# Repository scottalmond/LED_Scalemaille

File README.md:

# LED_Scalemaille
Neopixel Scalemaille

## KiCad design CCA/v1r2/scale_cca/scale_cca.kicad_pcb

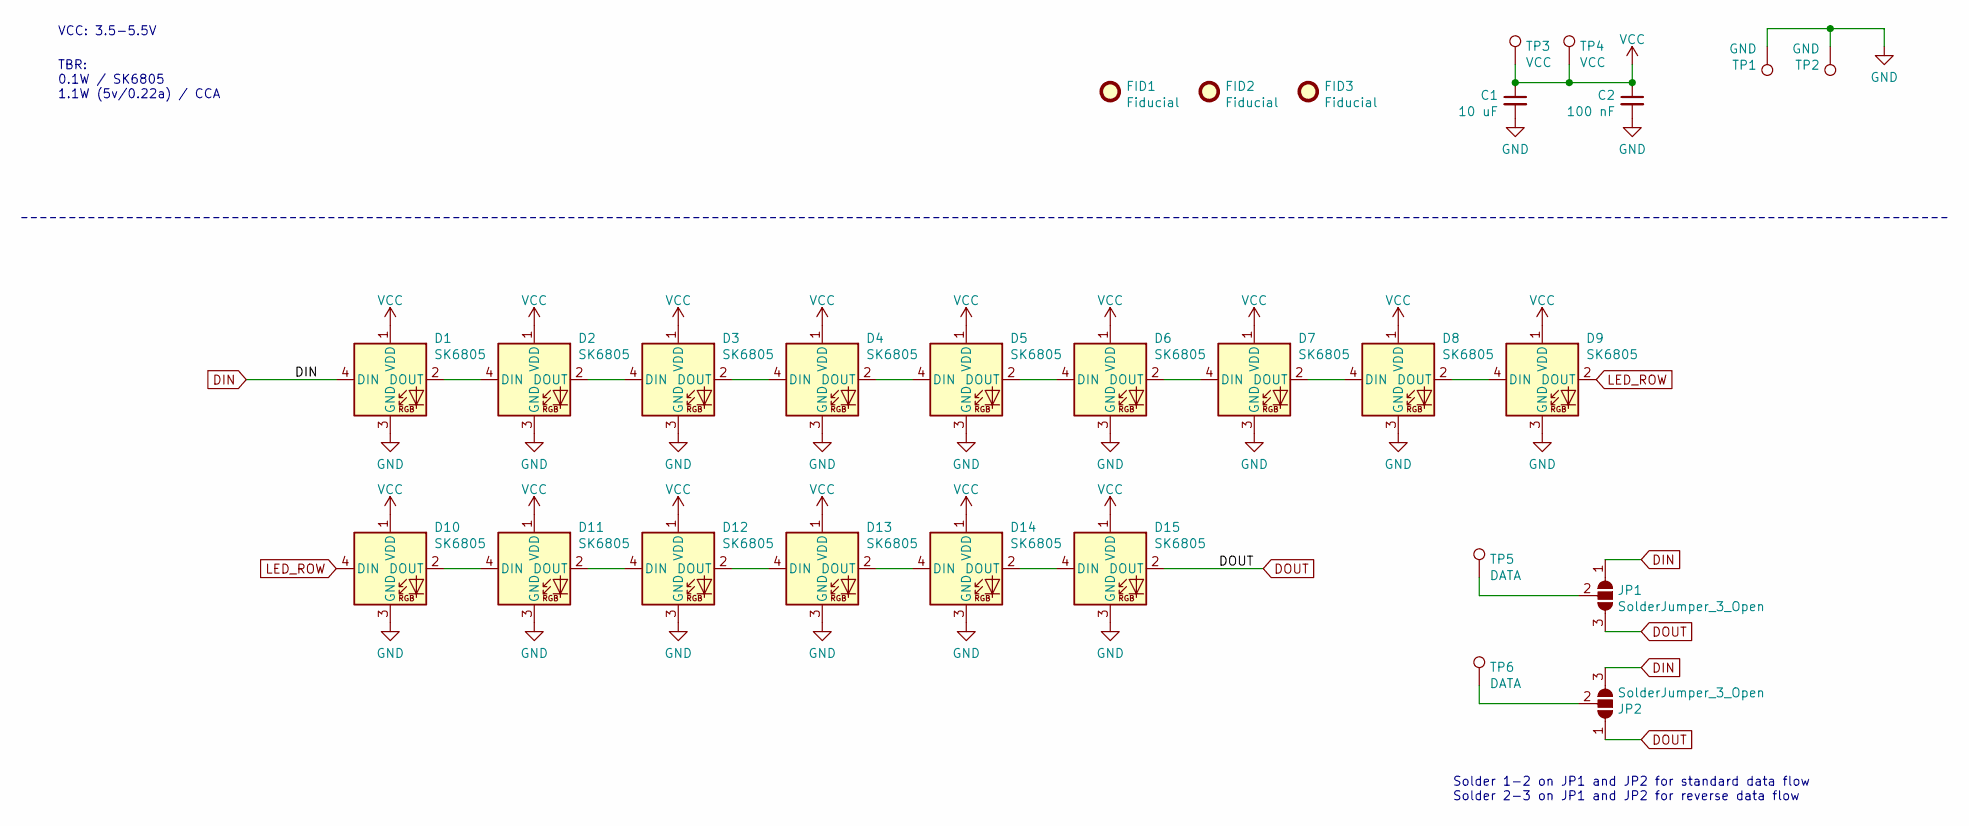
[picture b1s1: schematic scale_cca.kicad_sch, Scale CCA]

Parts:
C1: 10 uF; C_0805_2012Metric
C2: 100 nF; C_0805_2012Metric
D1, D2, D3, D4, D5, D6, D7, D8, D9, D10, D11, D12, D13, D14, D15: SK6805; LED_SK6805_2.0x2.0mm
FID1, FID2, FID3: Fiducial; Fiducial_0.5mm_Mask1mm
JP1, JP2: SolderJumper_3_Open; SolderJumper-3_P1.3mm_Open_RoundedPad1.0x1.5mm
TP1, TP2: GND; SMT_24AWG_Pad
TP3, TP4: VCC; SMT_24AWG_Pad
TP5, TP6: DATA; SMT_24AWG_Pad

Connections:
DIN: D1.4 (DIN), JP1.1 (A), JP2.3 (B)
DOUT: D15.2 (DOUT), JP1.3 (B), JP2.1 (A)
GND: C1.2, C2.2, D1.3 (GND), D2.3 (GND), D3.3 (GND), D4.3 (GND), D5.3 (GND), D6.3 (GND), D7.3 (GND), D8.3 (GND), D9.3 (GND), D10.3 (GND), D11.3 (GND), D12.3 (GND), D13.3 (GND), D14.3 (GND), D15.3 (GND), TP1.1, TP2.1
LED_ROW: D9.2 (DOUT), D10.4 (DIN)
unnamed: D1.2 (DOUT), D2.4 (DIN)
unnamed: D2.2 (DOUT), D3.4 (DIN)
unnamed: D3.2 (DOUT), D4.4 (DIN)
unnamed: D4.2 (DOUT), D5.4 (DIN)
unnamed: D5.2 (DOUT), D6.4 (DIN)
unnamed: D6.2 (DOUT), D7.4 (DIN)
unnamed: D7.2 (DOUT), D8.4 (DIN)
unnamed: D8.2 (DOUT), D9.4 (DIN)
unnamed: D10.2 (DOUT), D11.4 (DIN)
unnamed: D11.2 (DOUT), D12.4 (DIN)
unnamed: D12.2 (DOUT), D13.4 (DIN)
unnamed: D13.2 (DOUT), D14.4 (DIN)
unnamed: D14.2 (DOUT), D15.4 (DIN)
unnamed: JP1.2 (C), TP5.1
unnamed: JP2.2 (C), TP6.1
VCC: C1.1, C2.1, D1.1 (VDD), D2.1 (VDD), D3.1 (VDD), D4.1 (VDD), D5.1 (VDD), D6.1 (VDD), D7.1 (VDD), D8.1 (VDD), D9.1 (VDD), D10.1 (VDD), D11.1 (VDD), D12.1 (VDD), D13.1 (VDD), D14.1 (VDD), D15.1 (VDD), TP3.1, TP4.1

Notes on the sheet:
VCC: 3.5-5.5V
TBR: 0.1W / SK6805 1.1W (5v/0.22a) / CCA
Solder 1-2 on JP1 and JP2 for standard data flow Solder 2-3 on JP1 and JP2 for reverse data flow

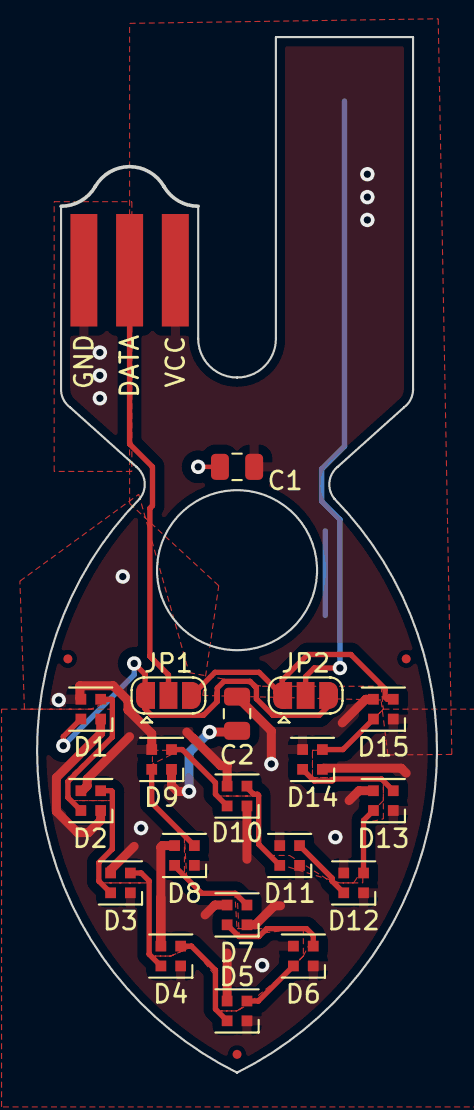
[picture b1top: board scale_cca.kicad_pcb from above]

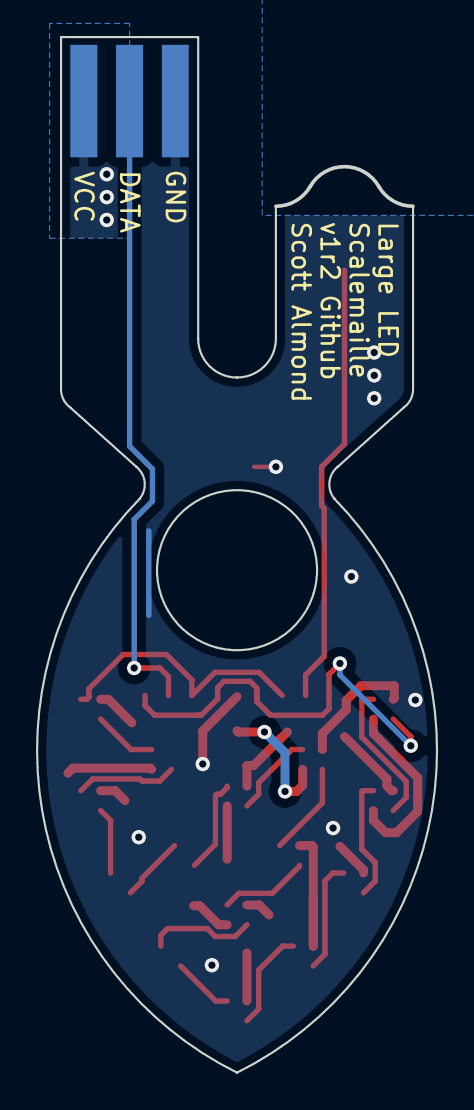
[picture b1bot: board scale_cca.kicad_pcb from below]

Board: 2 copper layers, 22.2 x 57.5 mm, 28 parts (3 on the bottom side), 20 nets.

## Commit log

2021-08-15 draft v1r0
2021-08-15 as built v1r0
2021-08-18 regenerated fab files for PCBWay
2021-09-01 stl files
2021-09-04 v1r1 as fabricated
2021-09-09 v2 of shell
2021-09-18 doc update
2021-10-04 v1r2 drafting
2021-10-11 pdf mock up
2021-10-25 mold
2021-11-09 v1r2 as built
